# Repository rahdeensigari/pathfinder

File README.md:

# pathfinder
Stasis starter project, now moved to Forge. Simple efidget PCB. This technically isn't my first PCB I've made, but all the past ones I've made were made with no guidance, so they were sort of terrible. I made this one from the tutorial that Hackclub provides, with some of my own modifications, like repositioning some components as well as adding a potentiometer to control the brightness of the LEDs.

# Schematic:

# PCB:

# [BOM](docs/BOM.pdf)
| Quantity                           | Name                      |   | Vendor      | Cost  | Link                                                                                                                                                                                                                                                                                                                                                                                                                                                                                                       |   |   |   |   |   |   |   | Notes      |
|------------------------------------|---------------------------|---|-------------|-------|------------------------------------------------------------------------------------------------------------------------------------------------------------------------------------------------------------------------------------------------------------------------------------------------------------------------------------------------------------------------------------------------------------------------------------------------------------------------------------------------------------|---|---|---|---|---|---|---|------------|
| 1                                  | PCB                       |   | JLCPCB      | $5.12 | https://jlcpcb.com                                                                                                                                                                                                                                                                                                                                                                                                                                                                                         |   |   |   |   |   |   |   |            |
| 1                                  | Xiao RP2040               |   | Aliexpress  | $9.23 | https://www.aliexpress.us/item/3256810568397753.html                                                                                                                                                                                                                                                                                                                                                                                                                                                       |   |   |   |   |   |   |   |            |
| 1                                  | 10KΩ Potentiometer        |   | Aliexpress  | $2.14 | https://www.aliexpress.us/item/3256806938094217.html                                                                                                                                                                                                                                                                                                                                                                                                                                                       |   |   |   |   |   |   |   | Out of 10  |
| 3                                  | 220Ω Resistor             |   | Amazon      | $4.99 | https://www.amazon.com/California-JOS-Resistance-CJ50-004-220/dp/B0BDKQSZHM/ref=sr_1_3?crid=16XMFPS0YQBG&dib=eyJ2IjoiMSJ9.pq8IXZtwkjU13efAoUQ012KAyknNA0lTscBiHFNwGQeYOwKh74jaeP0cnR0W_t07MlXJhoBuTpiAi_PkLW2RKGzjaWB_1C5_ExRWu060nO_F4Nx53aDlWP26C18R_qnazFIcb2tC-R1vdzEPu_x6jP4mFH4WMysbDzTQvrAIu-1RK8A7LAyXQxoX_HepcnQ0M6FZtUAyvWCoQOUzFDzshi68qsuJUMzXO_kr0tW38ek.bRjKB1IzgTTKU2bjAj3Flym5kEurwb2sg8c93M87ml4&dib_tag=se&keywords=220%2Bohm%2Bresistor&qid=1778371277&sprefix=%2Caps%2C114&sr=8-3&th=1 |   |   |   |   |   |   |   | Out of 100 |
| 1                                  | Red LED                   |   | Sparkfun    | $0.50 | https://www.sparkfun.com/led-basic-red-5mm.html                                                                                                                                                                                                                                                                                                                                                                                                                                                            |   |   |   |   |   |   |   |            |
| 1                                  | Green LED                 |   | Sparkfun    | $0.50 | https://www.sparkfun.com/led-basic-green-5mm.html                                                                                                                                                                                                                                                                                                                                                                                                                                                          |   |   |   |   |   |   |   |            |
| 1                                  | Blue LED                  |   | Sparkfun    | $0.75 | https://www.sparkfun.com/led-basic-blue-5mm.html                                                                                                                                                                                                                                                                                                                                                                                                                                                           |   |   |   |   |   |   |   |            |
| 3                                  | Gateron Baby Kangaroo 2.0 |   | KeebsForAll | $1.80 | https://keebsforall.com/products/gateron-baby-kangaroo-2-0-tactile-switches?_pos=1&_sid=2f2752f1a&_ss=r                                                                                                                                                                                                                                                                                                                                                                                                    |   |   |   |   |   |   |   |            |
| 3                                  | Keycaps                   |   | 3DP         |       |

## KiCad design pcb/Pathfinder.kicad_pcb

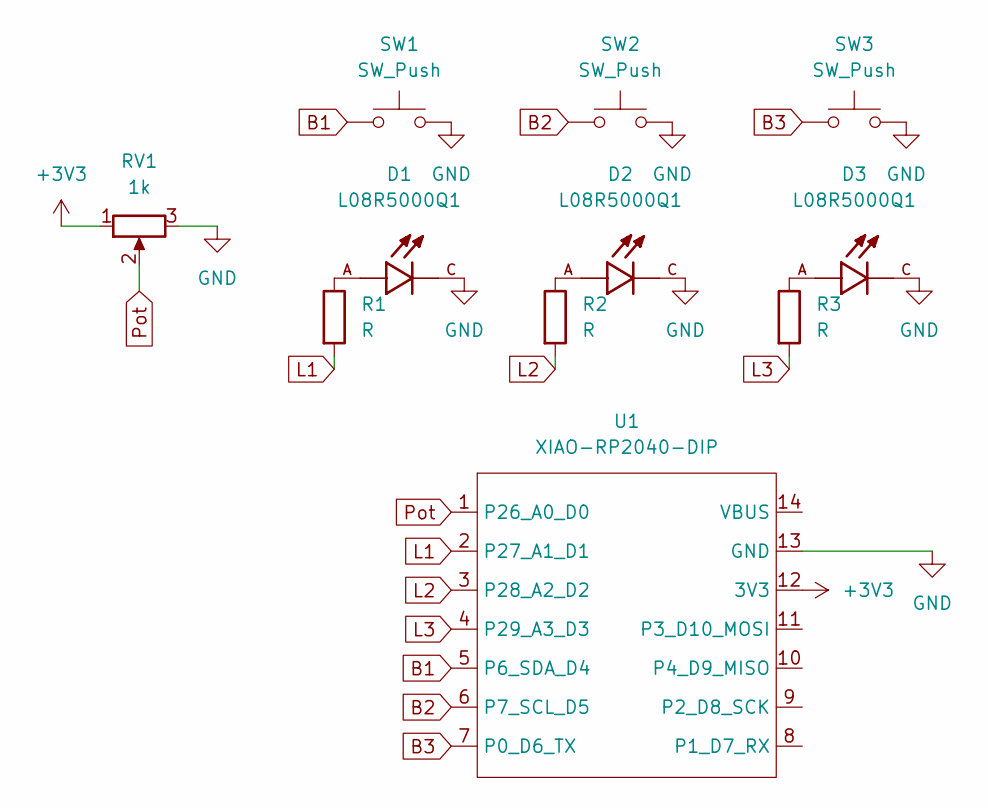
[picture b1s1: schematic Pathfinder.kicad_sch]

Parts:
D1, D2, D3: L08R5000Q1; LEDRD254W57D500H1070; PARTREV NA
R1, R2, R3: R; R_Axial_DIN0204_L3.6mm_D1.6mm_P5.08mm_Horizontal
RV1: 1k; Potentiometer_Bourns_3386W_Horizontal
SW1, SW2, SW3: SW_Push; SW_Cherry_MX_1.00u_PCB
U1: XIAO-RP2040-DIP

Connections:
+3V3: RV1.1, U1.12 (3V3)
B1: SW1.1, U1.5 (P6_SDA_D4)
B2: SW2.1, U1.6 (P7_SCL_D5)
B3: SW3.1, U1.7 (P0_D6_TX)
GND: D1.C, D2.C, D3.C, RV1.3, SW1.2, SW2.2, SW3.2, U1.13 (GND)
L1: R1.2, U1.2 (P27_A1_D1)
L2: R2.2, U1.3 (P28_A2_D2)
L3: R3.2, U1.4 (P29_A3_D3)
unnamed: D1.A, R1.1
unnamed: D2.A, R2.1
unnamed: D3.A, R3.1
Pot: RV1.2, U1.1 (P26_A0_D0)

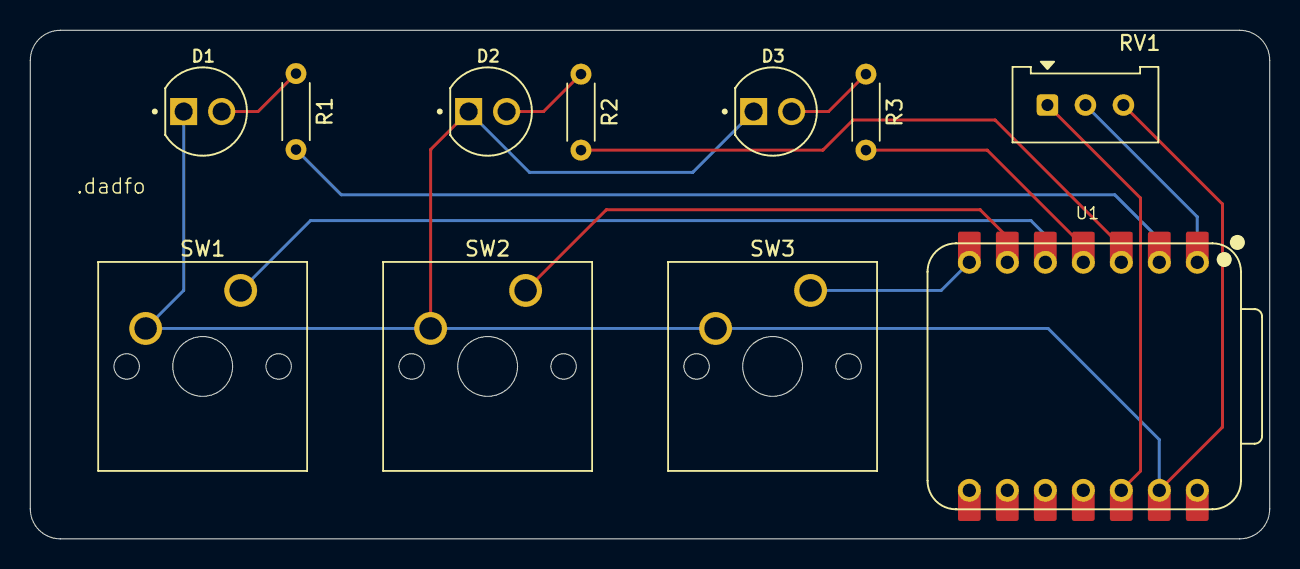
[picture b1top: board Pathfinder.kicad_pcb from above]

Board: 2 copper layers, 82.9 x 34.0 mm, 11 parts (0 on the bottom side), 12 nets.

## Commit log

2026-05-09 Create placeholder
2026-05-30 Rename Pathfinder BOM.csv to BOM.csv
2026-05-30 Rename Pathfinder BOM.pdf to PathfinderBOM.pdf
2026-06-03 Create a
